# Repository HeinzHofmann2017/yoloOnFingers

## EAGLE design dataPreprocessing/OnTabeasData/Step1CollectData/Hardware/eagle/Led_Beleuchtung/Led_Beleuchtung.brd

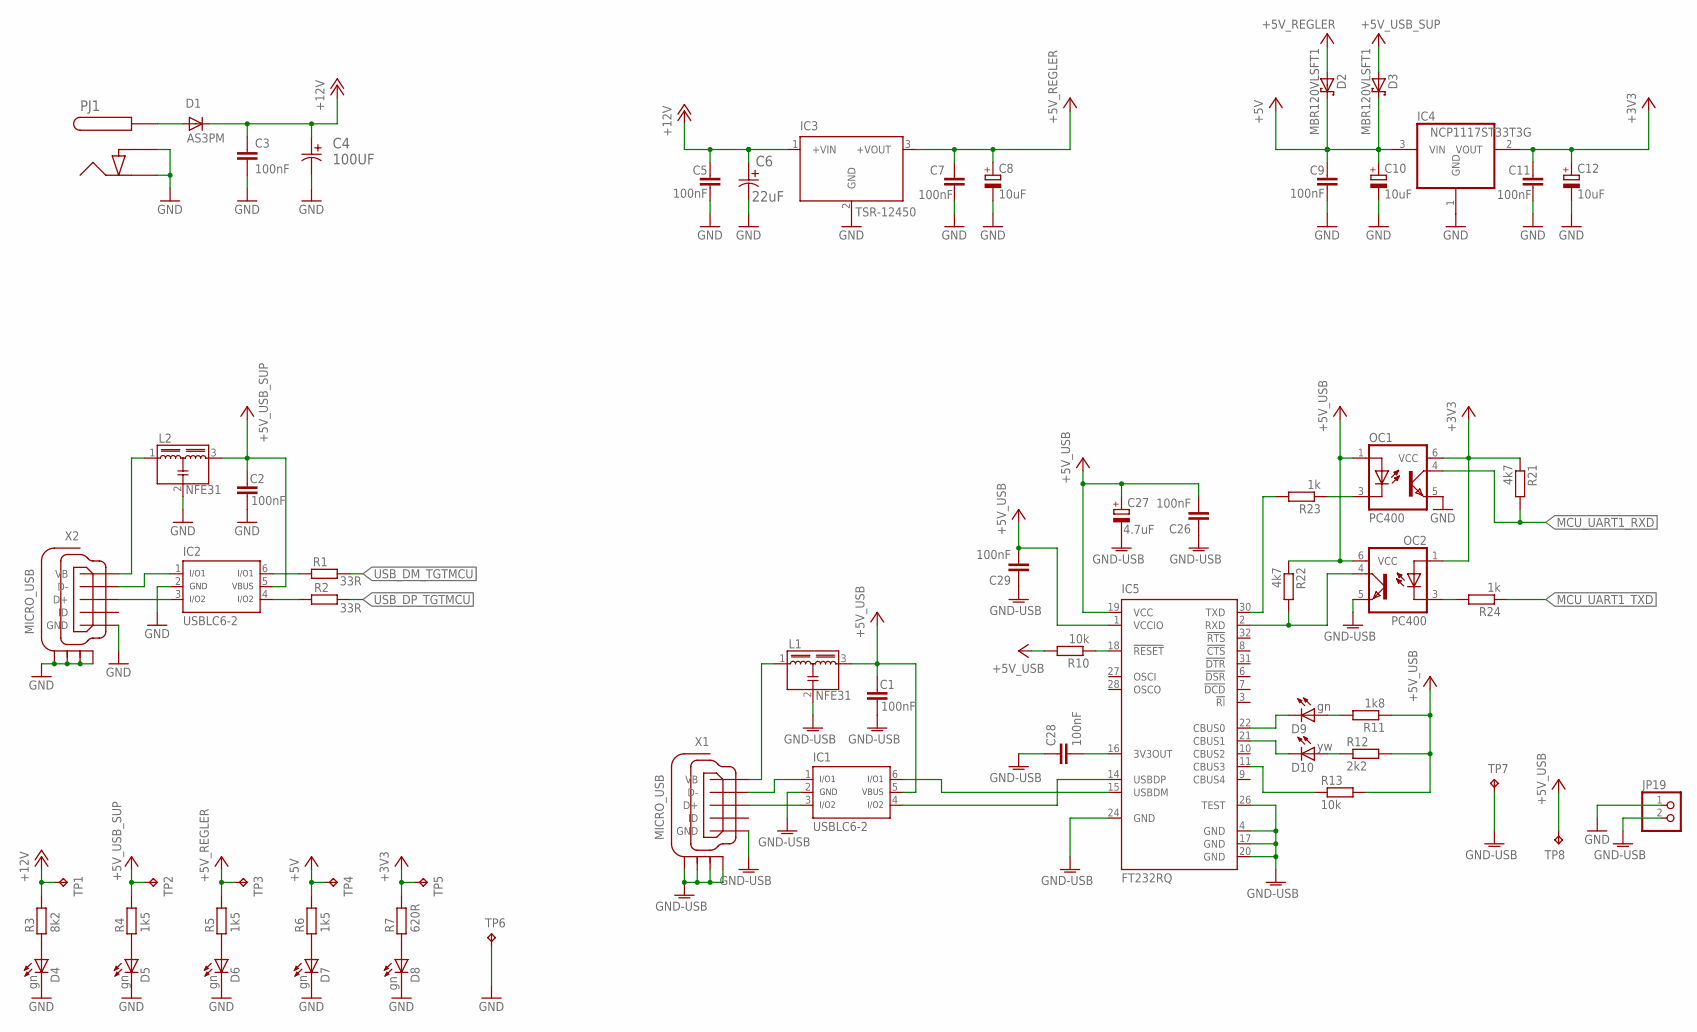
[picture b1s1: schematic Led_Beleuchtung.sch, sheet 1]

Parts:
C1, C2, C3, C5, C7, C9, C11, C26, C28: 100nF; C0603K
C4: 100UF; CAPAE660X800N
C6: 22uF; CAPAE660X610N
C8, C10, C12: 10uF; SMC_P
C27: 4.7uF; SMC_P
C29: 100nF; C0603
D1: AS3PM; TO-277A
D2, D3: MBR120VLSFT1; SOD-123
D4, D5, D6, D7, D8, D9: gn; CHIP-LED0603
D10: yw; CHIP-LED0603
IC1, IC2: USBLC6-2; SOT-23-6L
IC3: TSR-12450; TSR-1
IC4: NCP1117ST33T3G; SOT223
IC5: FT232RQ; QFN32
JP19: PINHD-1X2; 1X02
L1, L2: NFE31; EMIFILTER
OC1, OC2: PC400
PJ1: PJ-002AH-SMT-TR
R1, R2: 33R; R0603
R3: 8k2; R0603
R4, R5, R6: 1k5; R0603
R7: 620R; R0603
R10, R13: 10k; R0603
R11: 1k8; R0603
R12: 2k2; R0603
R21, R22: 4k7; R0603
R23, R24: 1k; R0603
TP1: +12V; TP08R
TP2: +5V_USB; TP08R
TP3: +5V_Reg; TP08R
TP4, TP8: +5V; TP08R
TP5: +3V3; TP08R
TP6, TP7: GND; TP08R
X1, X2: MICRO_USB; MICRO-USB

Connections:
3V3OUT_FT232: C28.2, IC5.16 (3V3OUT)
+3V3: C11.2, C12.+, IC4.2 (VOUT), OC1.6 (VCC), OC2.1 (A), R7.2, R21.1, TP5.TP; also elsewhere on the board
+5V: C9.2, C10.+, D2.C, D3.C, IC4.3 (VIN), R6.2, TP4.TP; also elsewhere on the board
+5V_REGLER: C7.2, C8.+, D2.A, IC3.3 (+VOUT), R5.2, TP3.TP
+5V_USB: C1.2, C26.2, C27.+, C29.2, IC1.5, IC5.1 (VCCIO), IC5.19 (VCC), L1.3, OC1.1 (A), OC2.6 (VCC), R10.2, R11.1, R12.2, R13.2, R22.1, TP8.TP
+5V_USB_SUP: C2.2, D3.A, IC2.5, L2.3, R4.2, TP2.TP
+12V: C3.2, C4.1, C5.2, C6.1, D1.C, IC3.1 (+VIN), R3.2, TP1.TP; also elsewhere on the board
GND: C2.1, C3.1, C4.2, C5.1, C6.2, C7.1, C8.-, C9.1, C10.-, C11.1, C12.-, D4.C, D5.C, D6.C, D7.C, D8.C, IC2.2, IC3.2 (GND), IC4.1 (GND), JP19.1, L2.2, OC1.5 (EMI), PJ1.2, PJ1.3, TP6.TP, X2.5 (GND), X2.GND1 (S1), X2.GND2 (S2), X2.GND3 (S3), X2.GND4 (S4); also elsewhere on the board
GND-USB: C1.1, C26.1, C27.-, C28.1, C29.1, IC1.2, IC5.4 (GND), IC5.17 (GND), IC5.20 (GND), IC5.24 (GND), IC5.26 (TEST), JP19.2, L1.2, OC2.5 (EMI), TP7.TP, X1.5 (GND), X1.GND1 (S1), X1.GND2 (S2), X1.GND3 (S3), X1.GND4 (S4)
MCU_UART1_RXD: OC1.4 (COL), R21.2; also elsewhere on the board
MCU_UART1_TXD: R24.1; also elsewhere on the board
unnamed: IC5.18 (!RESET), R10.1
unnamed: D9.C, IC5.22 (CBUS0)
unnamed: L1.1, X1.1 (VB)
unnamed: IC1.1, X1.2 (D-)
unnamed: IC1.3, X1.3 (D+)
unnamed: D4.A, R3.1
unnamed: L2.1, X2.1 (VB)
unnamed: D5.A, R4.1
unnamed: D10.C, IC5.21 (CBUS1)
unnamed: D10.A, R12.1
unnamed: D9.A, R11.2
unnamed: IC5.11 (CBUS3), R13.1
unnamed: IC2.1, X2.2 (D-)
unnamed: IC2.3, X2.3 (D+)
unnamed: IC2.4, R2.1
unnamed: IC2.6, R1.1
unnamed: D6.A, R5.1
unnamed: D1.A1 (A), D1.A2 (A), PJ1.1.1 (1), PJ1.1.2 (1)
unnamed: D7.A, R6.1
unnamed: D8.A, R7.1
unnamed: OC1.3 (C), R23.1
unnamed: OC2.3 (C), R24.2
unnamed: IC5.30 (TXD), R23.2
unnamed: IC5.2 (RXD), OC2.4 (COL), R22.2
USB_DM_FT232: IC1.6, IC5.15 (USBDM)
USB_DM_TGTMCU: R1.2; also elsewhere on the board
USB_DP_FT232: IC1.4, IC5.14 (USBDP)
USB_DP_TGTMCU: R2.2; also elsewhere on the board

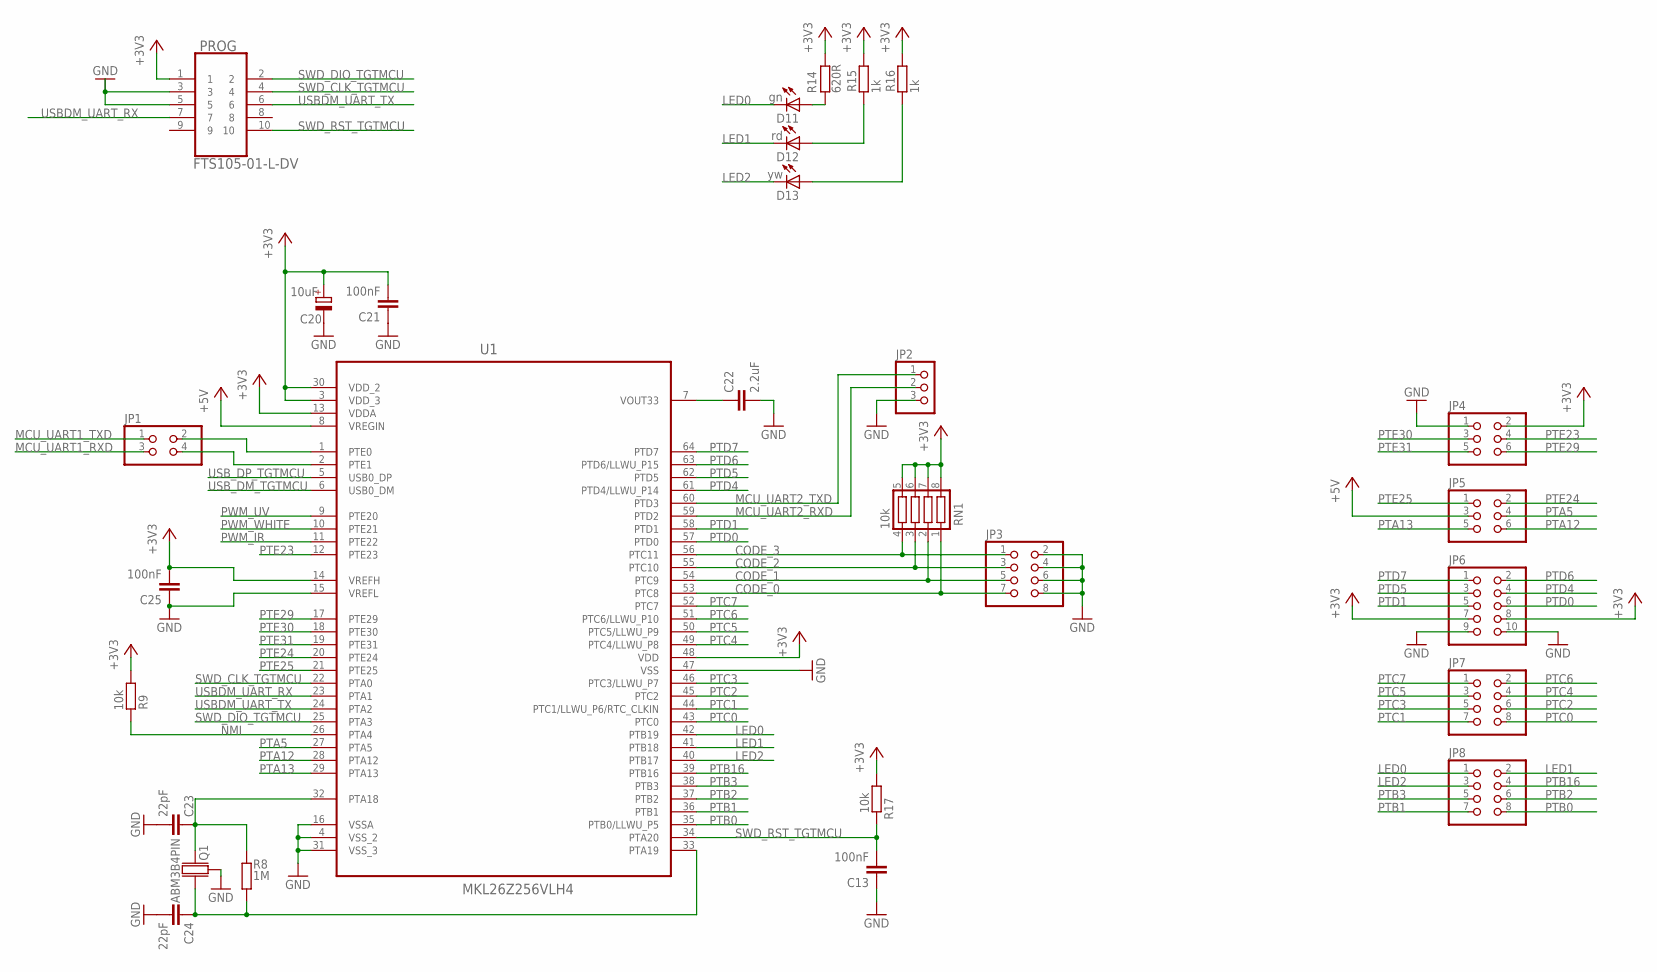
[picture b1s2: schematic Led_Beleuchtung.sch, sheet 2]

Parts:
C13, C21: 100nF; C0603
C20: 10uF; SMC_P
C22: 2.2uF; C0603
C23, C24: 22pF; C0603
C25: 100nF; C0603K
D11: gn; CHIP-LED0603
D12: rd; CHIP-LED0603
D13: yw; CHIP-LED0603
JP1: PINHD-2X2; 2X02
JP2: BCH-381H-3GN
JP3, JP7, JP8: PINHD-2X4; 2X04
JP4, JP5: PINHD-2X3; 2X03
JP6: PINHD-2X5; 2X05
PROG: FTS105-01-L-DV; SAMTEC_FTS105-01-L-DV
Q1: ABM3B4PIN; ABM3B
R8: 1M; R0603
R9, R17: 10k; R0603
R14: 620R; R0603
R15, R16: 1k; R0603
RN1: 10k; CTS742C083
U1: MKL26Z256VLH4; QFP50P1200X1200X160-64N

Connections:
+3V3: C20.+, C21.2, C25.2, JP4.2, JP6.7, JP6.8, PROG.1, R9.1, R14.2, R15.2, R16.2, R17.1, RN1.5, RN1.6, RN1.7, RN1.8, U1.3 (VDD_3), U1.13 (VDDA), U1.14 (VREFH), U1.30 (VDD_2), U1.48 (VDD); also elsewhere on the board
+5V: JP5.3, U1.8 (VREGIN); also elsewhere on the board
CODE_0: JP3.7, RN1.1, U1.53 (PTC8)
CODE_1: JP3.5, RN1.2, U1.54 (PTC9)
CODE_2: JP3.3, RN1.3, U1.55 (PTC10)
CODE_3: JP3.1, RN1.4, U1.56 (PTC11)
GND: C13.1, C20.-, C21.1, C22.2, C23.2, C24.2, C25.1, JP2.3, JP3.2, JP3.4, JP3.6, JP3.8, JP4.1, JP6.9, JP6.10, PROG.3, PROG.5, Q1.GND1 (GND), Q1.GND2 (GND), U1.4 (VSS_2), U1.15 (VREFL), U1.16 (VSSA), U1.31 (VSS_3), U1.47 (VSS); also elsewhere on the board
LED0: D11.C, JP8.1, U1.42 (PTB19)
LED1: D12.C, JP8.2, U1.41 (PTB18)
LED2: D13.C, JP8.3, U1.40 (PTB17)
MCU_UART1_RXD: JP1.3; also elsewhere on the board
MCU_UART1_TXD: JP1.1; also elsewhere on the board
MCU_UART2_RXD: JP2.2, U1.59 (PTD2)
MCU_UART2_TXD: JP2.1, U1.60 (PTD3)
unnamed: C23.1, Q1.1, R8.2, U1.32 (PTA18)
unnamed: C24.1, Q1.3 (2), R8.1, U1.33 (PTA19)
unnamed: D11.A, R14.1
unnamed: D12.A, R15.1
unnamed: D13.A, R16.1
unnamed: C22.1, U1.7 (VOUT33)
unnamed: JP1.2, U1.1 (PTE0)
unnamed: JP1.4, U1.2 (PTE1)
NMI: R9.2, U1.26 (PTA4)
PTA5: JP5.4, U1.27 (PTA5)
PTA12: JP5.6, U1.28 (PTA12)
PTA13: JP5.5, U1.29 (PTA13)
PTB0: JP8.8, U1.35 (PTB0/LLWU_P5)
PTB1: JP8.7, U1.36 (PTB1)
PTB2: JP8.6, U1.37 (PTB2)
PTB3: JP8.5, U1.38 (PTB3)
PTB16: JP8.4, U1.39 (PTB16)
PTC0: JP7.8, U1.43 (PTC0)
PTC1: JP7.7, U1.44 (PTC1/LLWU_P6/RTC_CLKIN)
PTC2: JP7.6, U1.45 (PTC2)
PTC3: JP7.5, U1.46 (PTC3/LLWU_P7)
PTC4: JP7.4, U1.49 (PTC4/LLWU_P8)
PTC5: JP7.3, U1.50 (PTC5/LLWU_P9)
PTC6: JP7.2, U1.51 (PTC6/LLWU_P10)
PTC7: JP7.1, U1.52 (PTC7)
PTD0: JP6.6, U1.57 (PTD0)
PTD1: JP6.5, U1.58 (PTD1)
PTD4: JP6.4, U1.61 (PTD4/LLWU_P14)
PTD5: JP6.3, U1.62 (PTD5)
PTD6: JP6.2, U1.63 (PTD6/LLWU_P15)
PTD7: JP6.1, U1.64 (PTD7)
PTE23: JP4.4, U1.12 (PTE23)
PTE24: JP5.2, U1.20 (PTE24)
PTE25: JP5.1, U1.21 (PTE25)
PTE29: JP4.6, U1.17 (PTE29)
PTE30: JP4.3, U1.18 (PTE30)
PTE31: JP4.5, U1.19 (PTE31)
PWM_IR: U1.11 (PTE22); also elsewhere on the board
PWM_UV: U1.9 (PTE20); also elsewhere on the board
PWM_WHITE: U1.10 (PTE21); also elsewhere on the board
SWD_CLK_TGTMCU: PROG.4, U1.22 (PTA0)
SWD_DIO_TGTMCU: PROG.2, U1.25 (PTA3)
SWD_RST_TGTMCU: C13.2, PROG.10, R17.2, U1.34 (PTA20)
USBDM_UART_RX: PROG.7, U1.23 (PTA1)
USBDM_UART_TX: PROG.6, U1.24 (PTA2)
USB_DM_TGTMCU: U1.6 (USB0_DM); also elsewhere on the board
USB_DP_TGTMCU: U1.5 (USB0_DP); also elsewhere on the board

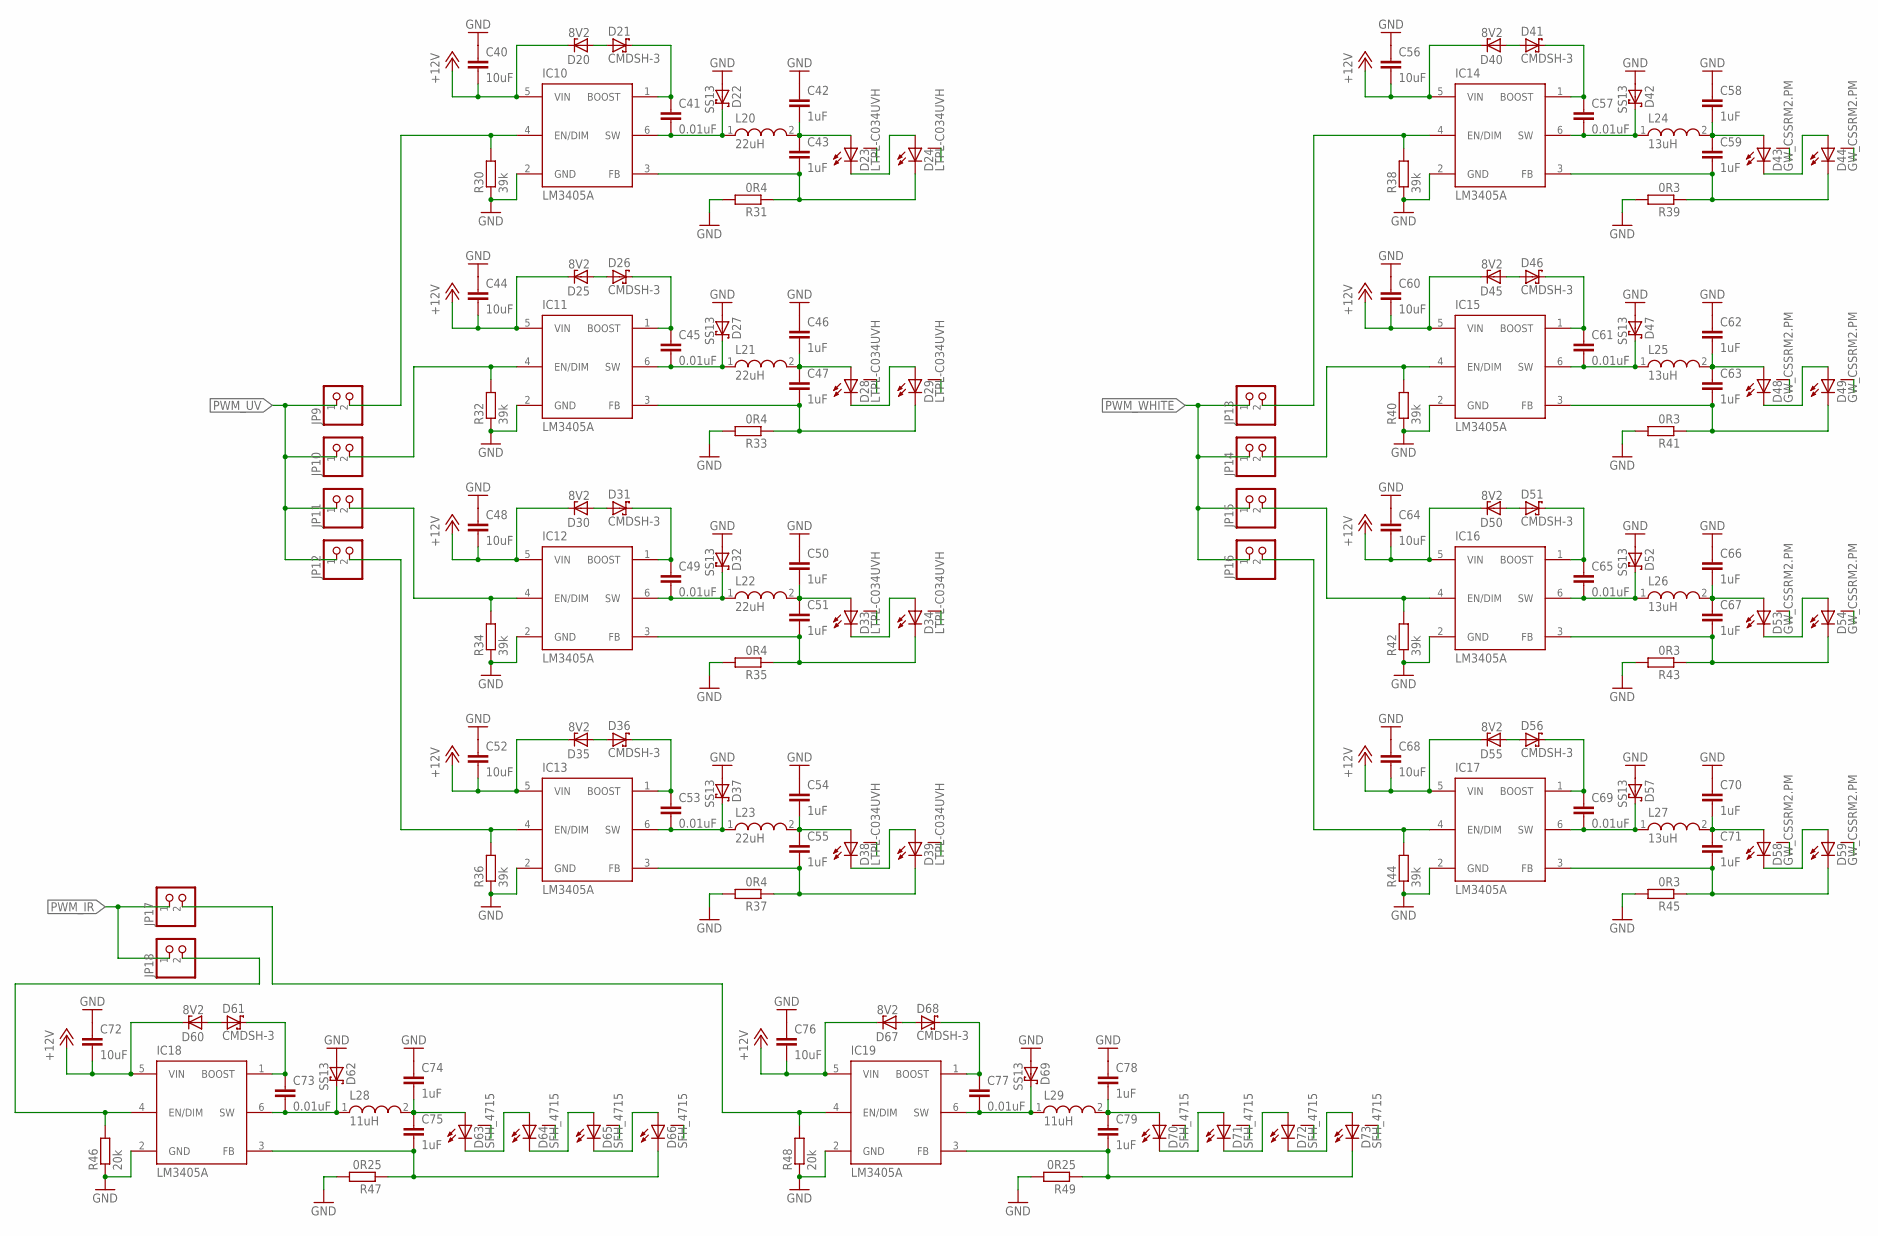
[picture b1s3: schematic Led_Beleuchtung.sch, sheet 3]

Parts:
C40, C44, C48, C52, C56, C60, C64, C68, C72, C76: 10uF; C1206K
C41, C45, C49, C53, C57, C61, C65, C69, C73, C77: 0.01uF; C0805K
C42, C43, C46, C47, C50, C51, C54, C55, C58, C59, C62, C63, C66, C67, C70, C71, C74, C75, C78, C79: 1uF; C1206K
D20, D25, D30, D35, D40, D45, D50, D55, D60, D67: 8V2; SOT23
D21, D26, D31, D36, D41, D46, D51, D56, D61, D68: CMDSH-3; SOD323
D22, D27, D32, D37, D42, D47, D52, D57, D62, D69: SS13; DO-214AC
D23, D24, D28, D29, D33, D34, D38, D39: LTPL-C034UVH
D43, D44, D48, D49, D53, D54, D58, D59: GW_CSSRM2.PM
D63, D64, D65, D66, D70, D71, D72, D73: SFH_4715
IC10, IC11, IC12, IC13, IC14, IC15, IC16, IC17, IC18, IC19: LM3405A; DDC6_SOT
JP9, JP10, JP11, JP12, JP13, JP14, JP15, JP16, JP17, JP18: PINHD-1X2; 1X02
L20, L21, L22, L23: 22uH; WE-PDF
L24, L25, L26, L27: 13uH; WE-PDF
L28, L29: 11uH; WE-PDF
R30, R32, R34, R36, R38, R40, R42, R44: 39k; R0603
R31, R33, R35, R37: 0R4; R2010
R39, R41, R43, R45: 0R3; R2010
R46, R48: 20k; R0603
R47, R49: 0R25; R2010

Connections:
+12V: C40.2, C44.2, C48.2, C52.2, C56.2, C60.2, C64.2, C68.2, C72.2, C76.2, D20.3 (C), D25.3 (C), D30.3 (C), D35.3 (C), D40.3 (C), D45.3 (C), D50.3 (C), D55.3 (C), D60.3 (C), D67.3 (C), IC10.5 (VIN), IC11.5 (VIN), IC12.5 (VIN), IC13.5 (VIN), IC14.5 (VIN), IC15.5 (VIN), IC16.5 (VIN), IC17.5 (VIN), IC18.5 (VIN), IC19.5 (VIN); also elsewhere on the board
GND: C40.1, C42.1, C44.1, C46.1, C48.1, C50.1, C52.1, C54.1, C56.1, C58.1, C60.1, C62.1, C64.1, C66.1, C68.1, C70.1, C72.1, C74.1, C76.1, C78.1, D22.A, D27.A, D32.A, D37.A, D42.A, D47.A, D52.A, D57.A, D62.A, D69.A, IC10.2 (GND), IC11.2 (GND), IC12.2 (GND), IC13.2 (GND), IC14.2 (GND), IC15.2 (GND), IC16.2 (GND), IC17.2 (GND), IC18.2 (GND), IC19.2 (GND), R30.1, R31.2, R32.1, R33.2, R34.1, R35.2, R36.1, R37.2, R38.1, R39.2, R40.1, R41.2, R42.1, R43.2, R44.1, R45.2, R46.1, R47.2, R48.1, R49.2; also elsewhere on the board
LED_WHITE8: D58.C, D59.A
unnamed: C77.1, D68.C, IC19.1 (BOOST)
unnamed: D67.1 (A), D68.A
unnamed: C77.2, D69.C, IC19.6 (SW), L29.1
unnamed: C78.2, C79.1, D70.A, L29.2
unnamed: D70.C, D71.A
unnamed: D71.C, D72.A
unnamed: D72.C, D73.A
unnamed: C79.2, D73.C, IC19.3 (FB), R49.1
unnamed: C57.1, D41.C, IC14.1 (BOOST)
unnamed: C73.1, D61.C, IC18.1 (BOOST)
unnamed: D60.1 (A), D61.A
unnamed: C73.2, D62.C, IC18.6 (SW), L28.1
unnamed: C74.2, C75.1, D63.A, L28.2
unnamed: D63.C, D64.A
unnamed: D64.C, D65.A
unnamed: D65.C, D66.A
unnamed: C75.2, D66.C, IC18.3 (FB), R47.1
unnamed: D40.1 (A), D41.A
unnamed: C57.2, D42.C, IC14.6 (SW), L24.1
unnamed: C58.2, C59.1, D43.A, L24.2
unnamed: D43.C, D44.A
unnamed: C61.1, D46.C, IC15.1 (BOOST)
unnamed: D45.1 (A), D46.A
unnamed: C59.2, D44.C, IC14.3 (FB), R39.1
unnamed: C61.2, D47.C, IC15.6 (SW), L25.1
unnamed: C62.2, C63.1, D48.A, L25.2
unnamed: D48.C, D49.A
unnamed: C63.2, D49.C, IC15.3 (FB), R41.1
unnamed: C65.1, D51.C, IC16.1 (BOOST)
unnamed: D50.1 (A), D51.A
unnamed: C65.2, D52.C, IC16.6 (SW), L26.1
unnamed: C66.2, C67.1, D53.A, L26.2
unnamed: D53.C, D54.A
unnamed: C67.2, D54.C, IC16.3 (FB), R43.1
unnamed: C69.1, D56.C, IC17.1 (BOOST)
unnamed: D55.1 (A), D56.A
unnamed: C69.2, D57.C, IC17.6 (SW), L27.1
unnamed: C70.2, C71.1, D58.A, L27.2
unnamed: C71.2, D59.C, IC17.3 (FB), R45.1
unnamed: C41.1, D21.C, IC10.1 (BOOST)
unnamed: D20.1 (A), D21.A
unnamed: C41.2, D22.C, IC10.6 (SW), L20.1
unnamed: C42.2, C43.1, D23.A, L20.2
unnamed: D23.C, D24.A
unnamed: C43.2, D24.C, IC10.3 (FB), R31.1
unnamed: C45.1, D26.C, IC11.1 (BOOST)
unnamed: D25.1 (A), D26.A
unnamed: C45.2, D27.C, IC11.6 (SW), L21.1
unnamed: C46.2, C47.1, D28.A, L21.2
unnamed: D28.C, D29.A
unnamed: C47.2, D29.C, IC11.3 (FB), R33.1
unnamed: C49.1, D31.C, IC12.1 (BOOST)
unnamed: D30.1 (A), D31.A
unnamed: C49.2, D32.C, IC12.6 (SW), L22.1
unnamed: C50.2, C51.1, D33.A, L22.2
unnamed: D33.C, D34.A
unnamed: C51.2, D34.C, IC12.3 (FB), R35.1
unnamed: C53.1, D36.C, IC13.1 (BOOST)
unnamed: D35.1 (A), D36.A
unnamed: C53.2, D37.C, IC13.6 (SW), L23.1
unnamed: C54.2, C55.1, D38.A, L23.2
unnamed: D38.C, D39.A
unnamed: C55.2, D39.C, IC13.3 (FB), R37.1
unnamed: IC10.4 (EN/DIM), JP9.2, R30.2
unnamed: IC11.4 (EN/DIM), JP10.2, R32.2
unnamed: IC12.4 (EN/DIM), JP11.2, R34.2
unnamed: IC13.4 (EN/DIM), JP12.2, R36.2
unnamed: IC14.4 (EN/DIM), JP13.2, R38.2
unnamed: IC15.4 (EN/DIM), JP14.2, R40.2
unnamed: IC16.4 (EN/DIM), JP15.2, R42.2
unnamed: IC17.4 (EN/DIM), JP16.2, R44.2
unnamed: IC18.4 (EN/DIM), JP18.2, R46.2
unnamed: IC19.4 (EN/DIM), JP17.2, R48.2
PWM_IR: JP17.1, JP18.1; also elsewhere on the board
PWM_UV: JP9.1, JP10.1, JP11.1, JP12.1; also elsewhere on the board
PWM_WHITE: JP13.1, JP14.1, JP15.1, JP16.1; also elsewhere on the board
TH_D23: D23.TH
TH_D24: D24.TH
TH_D28: D28.TH
TH_D29: D29.TH
TH_D33: D33.TH
TH_D34: D34.TH
TH_D38: D38.TH
TH_D39: D39.TH
TH_D43: D43.TH
TH_D44: D44.TH
TH_D48: D48.TH
TH_D49: D49.TH
TH_D53: D53.TH
TH_D54: D54.TH
TH_D58: D58.TH
TH_D59: D59.TH
TH_D63: D63.TH
TH_D64: D64.TH
TH_D65: D65.TH
TH_D66: D66.TH
TH_D70: D70.TH
TH_D71: D71.TH
TH_D72: D72.TH
TH_D73: D73.TH

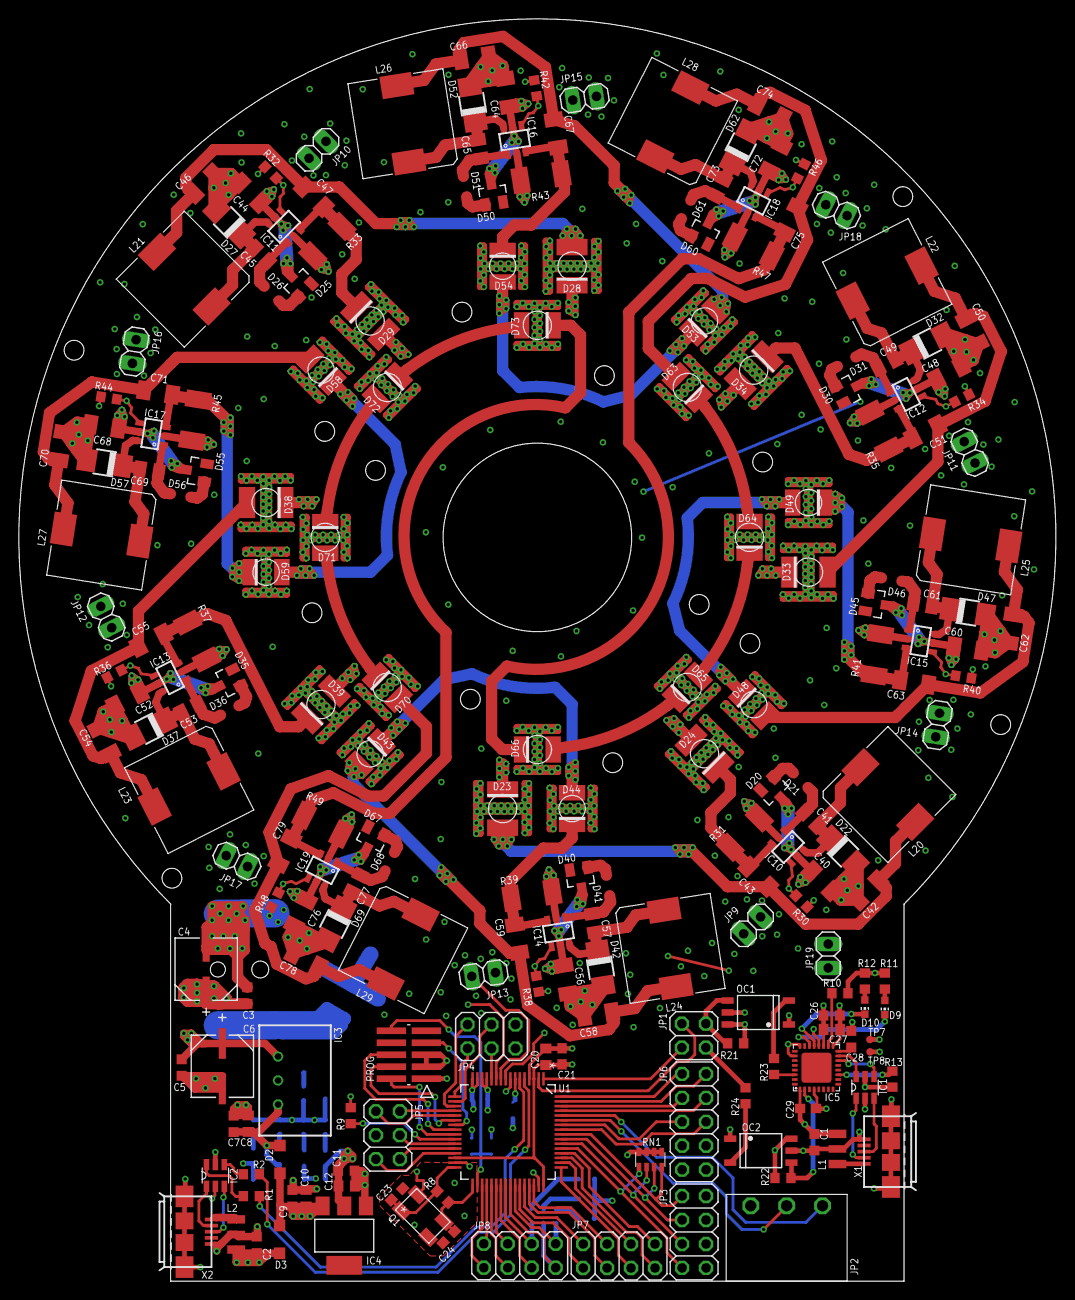
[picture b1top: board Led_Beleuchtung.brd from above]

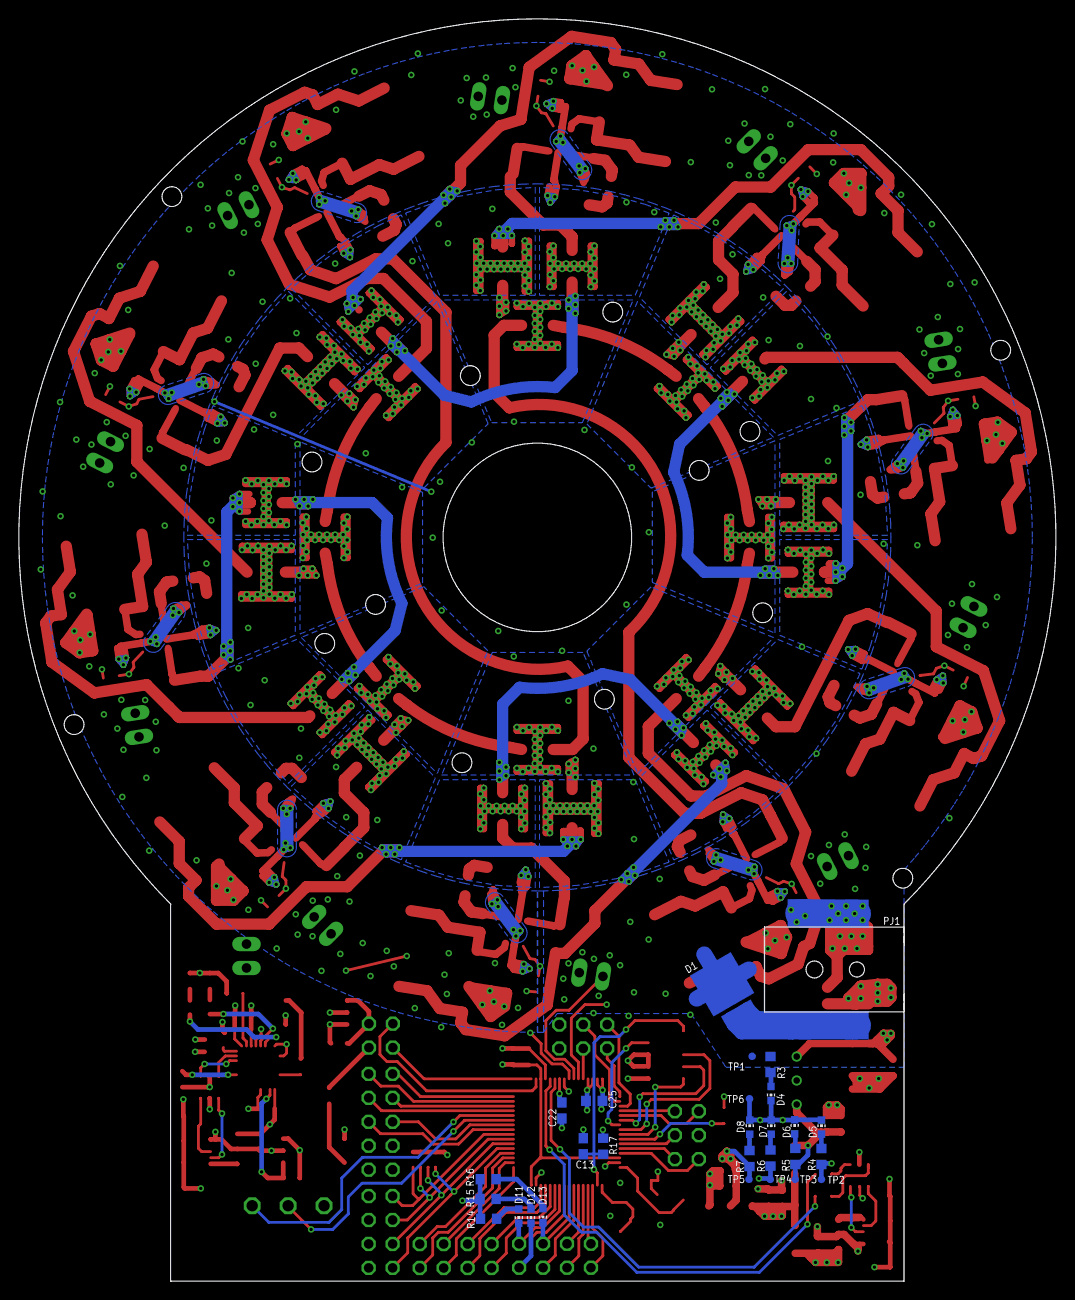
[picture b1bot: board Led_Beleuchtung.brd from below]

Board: 4 copper layers, 110.0 x 133.9 mm, 234 parts (28 on the bottom side), 167 nets.

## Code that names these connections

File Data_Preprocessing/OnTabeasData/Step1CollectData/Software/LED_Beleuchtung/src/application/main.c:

/**************************************************
    Projekt:        Led Illumination
    File:           main.c
    Date:           30.03.2017
    Author:         tmendez

    Description:    main-programm for turning
                    leds on an off via UART

**************************************************/

#include <MKL26Z4.h>
#include <MKL_EXT.h>

#include "uart.h"
#include "pwm.h"

#define LED_YELLOW  PIN_INV(PB,17)
#define LED_RED     PIN_INV(PB,18)
#define LED_GREEN   PIN_INV(PB,19)

#define CODE_0      PIN(PC,8)
#define CODE_1      PIN(PC,9)
#define CODE_2      PIN(PC,10)
#define CODE_3      PIN(PC,11)

void gpio_init(void);
void delay(void);

enum commands {UV_ON=0x81, IR_ON=0x82, WHITE_ON=0x84, OFF = 0x88};

int main(void)
{
    uint8_t error = 0;
    uint8_t timeout = 0;
    uint8_t led = 0;
    uint8_t pwmValue = 0;
    uint8_t valid = 0;
    uint8_t master = 0;

    gpio_init();
    pwm_init();
    uart_init(1,38400);
    uart_init(2,115200);
    master = ~INPUT_GET(CODE_0);

    // indicate master or slave
    if ( master == 1 ){
        OUTPUT_SET(LED_RED,POSITION_ON);
    } else {
        OUTPUT_SET(LED_YELLOW,POSITION_ON);
    }


    while(1) {

        if ( master == 1 ) {
            // Master listens at UART1 and forwards the command at UART2
            do {
                do {
                    // wait for data to receive at UART1
                    error = uart_rxChar(1, &led);
                }while(error);
                OUTPUT_SET(LED_GREEN,POSITION_ON);
                uart_rxChar(1, &pwmValue);
                pwmValue &= 0x7F;
                OUTPUT_SET(LED_GREEN,POSITION_OFF);
                switch( led ){
                    case UV_ON:     // turn on UV led
                        pwm_set(IR, 0);
                        pwm_set(WHITE, 0);
                        pwm_set(UV, pwmValue);

                        uart_txChar(2, UV_ON);
                        OUTPUT_SET(LED_GREEN,POSITION_ON);
                        uart_txChar(2, pwmValue);
                        OUTPUT_SET(LED_GREEN,POSITION_OFF);
                        valid = 1;
                        break;
                    case IR_ON:     // turn on IR led
                        pwm_set(UV, 0);
                        pwm_set(WHITE, 0);
                        pwm_set(IR, pwmValue);

                        uart_txChar(2, IR_ON);
                        OUTPUT_SET(LED_GREEN,POSITION_ON);
                        uart_txChar(2, pwmValue);
                        OUTPUT_SET(LED_GREEN,POSITION_OFF);
                        valid = 1;
                        break;
                    case WHITE_ON:  // turn on WHITE led
                        pwm_set(UV, 0);
                        pwm_set(IR, 0);
                        pwm_set(WHITE, pwmValue);

                        uart_txChar(2, WHITE_ON);
                        OUTPUT_SET(LED_GREEN,POSITION_ON);
                        uart_txChar(2, pwmValue);
                        OUTPUT_SET(LED_GREEN,POSITION_OFF);
                        valid = 1;
                        break;
                    case OFF:       // turn off leds
                        pwm_set(UV, 0);
                        pwm_set(IR, 0);
                        pwm_set(WHITE, 0);

                        uart_txChar(2, OFF);
                        OUTPUT_SET(LED_GREEN,POSITION_ON);
                        uart_txChar(2, pwmValue);
                        OUTPUT_SET(LED_GREEN,POSITION_OFF);
                        valid = 1;
                        break;
                    default:
                        // No valid command
                        uart_txChar(1,'e');
                        OUTPUT_SET(LED_GREEN,POSITION_ON);
                        uart_txChar(1,'r');
                        OUTPUT_SET(LED_GREEN,POSITION_OFF);
                        valid = 0;
                        break;
                }
            }while(valid == 0);
            valid = 0;

            // Master waits for the forwarded command to return at UART2
            // and answers at UART1
            timeout = 0;
            do{
                // wait for data to receive at UART2
                error = uart_rxChar(2, &led);
                timeout++;
            }while(error && timeout<10);
            OUTPUT_SET(LED_GREEN,POSITION_ON);
            uart_rxChar(2, &pwmValue);
            pwmValue &= 0x7F;
            OUTPUT_SET(LED_GREEN,POSITION_OFF);
            switch( led ){
                case UV_ON:
                    uart_txChar(1,UV_ON);
                    OUTPUT_SET(LED_GREEN,POSITION_ON);
                    uart_txChar(1, pwmValue);
                    OUTPUT_SET(LED_GREEN,POSITION_OFF);
                    break;
                case IR_ON:
                    uart_txChar(1,IR_ON);
                    OUTPUT_SET(LED_GREEN,POSITION_ON);
                    uart_txChar(1, pwmValue);
                    OUTPUT_SET(LED_GREEN,POSITION_OFF);
                    break;
                case WHITE_ON:
                    uart_txChar(1,WHITE_ON);
                    OUTPUT_SET(LED_GREEN,POSITION_ON);
                    uart_txChar(1, pwmValue);
                    OUTPUT_SET(LED_GREEN,POSITION_OFF);
                    break;
                case OFF:
                    uart_txChar(1,OFF);
                    OUTPUT_SET(LED_GREEN,POSITION_ON);
                    uart_txChar(1, pwmValue);
                    OUTPUT_SET(LED_GREEN,POSITION_OFF);
                    break;
                default:
                    // error occured
                    uart_txChar(1,'e');
                    OUTPUT_SET(LED_GREEN,POSITION_ON);
                    uart_txChar(1,'r');
                    OUTPUT_SET(LED_GREEN,POSITION_OFF);
                    break;
            }

        } else {

            // Slave listens at UART2 and forwards the command at UART2
            do{
                // wait for data to receive at UART2
                error = uart_rxChar(2, &led);
            }while(error);
            OUTPUT_SET(LED_GREEN,POSITION_ON);
            uart_rxChar(2, &pwmValue);
            pwmValue &= 0x7F;
            OUTPUT_SET(LED_GREEN,POSITION_OFF);
            switch( led ){
                case UV_ON:    // turn on UV led
                    pwm_set(IR, 0);
                    pwm_set(WHITE, 0);
                    pwm_set(UV, pwmValue);

                    uart_txChar(2, UV_ON);
                    OUTPUT_SET(LED_GREEN,POSITION_ON);
                    uart_txChar(2, pwmValue);
                    OUTPUT_SET(LED_GREEN,POSITION_OFF);
                    break;
                case IR_ON:    // turn on IR led
                    pwm_set(UV, 0);
                    pwm_set(WHITE, 0);
                    pwm_set(IR, pwmValue);

                    uart_txChar(2, IR_ON);
                    OUTPUT_SET(LED_GREEN,POSITION_ON);
                    uart_txChar(2, pwmValue);
                    OUTPUT_SET(LED_GREEN,POSITION_OFF);
                    break;
                case WHITE_ON:  // turn on WHITE led
                    pwm_set(UV, 0);
                    pwm_set(IR, 0);
                    pwm_set(WHITE, pwmValue);

                    uart_txChar(2, WHITE_ON);
                    OUTPUT_SET(LED_GREEN,POSITION_ON);
                    uart_txChar(2, pwmValue);
                    OUTPUT_SET(LED_GREEN,POSITION_OFF);
                    break;
                case OFF:       // turn off leds
                    pwm_set(UV, 0);
                    pwm_set(IR, 0);
                    pwm_set(WHITE, 0);

                    uart_txChar(2, OFF);
                    OUTPUT_SET(LED_GREEN,POSITION_ON);
                    uart_txChar(2, pwmValue);
                    OUTPUT_SET(LED_GREEN,POSITION_OFF);
                    break;
                default:
                    // error occured
                    uart_txChar(2,'e');
                    OUTPUT_SET(LED_GREEN,POSITION_ON);
                    uart_txChar(2,'r');
                    OUTPUT_SET(LED_GREEN,POSITION_OFF);
                    break;
            }
        }
    }
}

void gpio_init(void)
{
    // activate port-clocks
    SIM->SCGC5 =    SIM_SCGC5_PORTA_MASK |
                    SIM_SCGC5_PORTB_MASK |
                    SIM_SCGC5_PORTC_MASK |
                    SIM_SCGC5_PORTD_MASK |
                    SIM_SCGC5_PORTE_MASK;

    // init outputs of LED's
    INIT_OUTPUT(LED_YELLOW);
    OUTPUT_SET(LED_YELLOW, POSITION_OFF);
    INIT_OUTPUT(LED_RED);
    OUTPUT_SET(LED_RED, POSITION_OFF);
    INIT_OUTPUT(LED_GREEN);
    OUTPUT_SET(LED_GREEN, POSITION_OFF);

    // init inputs of master/slave-code
    INIT_INPUT_PULLUP(CODE_0);
    INIT_INPUT_PULLUP(CODE_1);
    INIT_INPUT_PULLUP(CODE_2);
    INIT_INPUT_PULLUP(CODE_3);
}

void delay(void)
{
    volatile unsigned int i,j;

    for (i = 0U; i < 5000U; i++) {
        for (j = 0U; j < 1000U; j++) {
            __asm__("nop");
        }
    }
}

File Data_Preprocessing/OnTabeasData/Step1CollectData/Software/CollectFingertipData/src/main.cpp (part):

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#define	IM_HEIGHT       960
#define N_CAMS          4

#define PWM_UV          100     // 0 ... 127
#define PWM_IR          0       // 0 ... 127
#define PWM_WHITE       40      // 0 ... 127

#define MAX_TRIALS      5

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
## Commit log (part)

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2017-10-25 probably really made the folder weights i guess
2017-10-25 just another string with numbers fixed
2017-10-25 bug in if-statement line 472 fixed, because of this this if statement never entered
2017-10-25 edited the code, so that the model will be saved in the share-Folder an not in the repository
2017-11-02 code merged together in one Repository(little cleanup)
2017-11-02 Versuch Hannes
2017-11-02 made condition for cropping data
2017-11-02 deletet old Pretrainingyolo directory...again..
2017-11-02 changed file to better work on relative-paths
2017-11-02 made second file for hannes s Test
2017-11-02 made function to convert pictures to grayscale with zeropadded minimumsize of 244*244
2017-11-03 better runtime-variables
2017-11-03 made validation for testset in % to test how accurate my model is
2017-11-03 rised badgesize up to 64 just to try
2017-11-03 reduced number of epochs, until model is saved again
2017-11-03 print the true prediction vector to shell
2017-11-03 changed the learning rate
2017-11-03 new order for scripts to run docker container
2017-11-03 some path correctures
2017-11-03 made second file to learn with higher learnrate
2017-11-03 corrected something wrong with the mailer
2017-11-06 changed name of shell-script
2017-11-06 added gradients to graph
2017-11-06 gradient multiplicated with 1000 for visualisation.
2017-11-06 set learning rate to 1
2017-11-07 made batchnorm and function to create convolutional-layers
2017-11-07 took b from the convolutional layers, because it isn't important anymore since batchnorm and we need free memory on dgx
2017-11-07 still wasn't enough free space, make Batchsize = 1
2017-11-07 plugin batchnorm one after the other, first without batchnorm again
2017-11-07 aölsdkfj
2017-11-07 aölsf
2017-11-07 changed graphiccard
2017-11-07 made learning-rate smaller, because of histogram-crash because of infinite numbers in the third iteration and made batchsize greater from 1 to 128
2017-11-07 worked fine, now enable for ca. 10 Layers batchnorm
2017-11-07 works fine now, no Problems with memory, the problem was the other GPU was allreasy in use. Lets train now over the night
2017-11-08 testing give name to shellscript
2017-11-08 optimized training-loop, so there is no if-statement in the loop anymore
2017-11-08 little change in the name of the summarys
2017-11-09 E-Mail is now better configured, so we have the name of the model on the mail too
2017-11-09 made script for running things on gpu 3
2017-11-09 better initialized Weights
2017-11-09 fixed mistake in Graph
2017-11-09 better weight init didn't work, the gradients vanished much harder than before...
2017-11-10 little bugfix
2017-11-10 used the wrong GPU
2017-11-10 The Problem with the visualisation of the error was, that the output of the network had one dimension too much for comparing with the labels.
2017-11-10 Adam instead of gradientDescent applied
2017-11-10 reverse change that console-output will be written to logfile, because it didn't work well...
2017-11-10 made a bigger epsilon in the adam-converter, because i guess this made nans for the tensorboard
2017-11-18 batchnorm is now before relu instead after relu
2017-11-20 introduced capped grads and vars, so there should no NAN's anymore, when the Wheights from Layer 1,5 or 22 is tryed to save for tensorboard.
2017-11-21 reorganized folder-structure with shellscripts to start docker and programms.
2017-11-22 started to make trainprogramm for fingers with weights from pretraining, but there are some problems with the tensorflow saver
2017-11-22 commented out cv2, because in the docker this package isn't included...
2017-11-22 made correct path in the shell-script
2017-11-22 disabled batchnorm and dropout and hope, now there is enough space in the memory
2017-11-22 made batchSize 8 and bufferSize for shuffling 500
2017-11-22 batchsize reduced to 1 and enabled dropout again ...
2017-11-22 there was no error, but there where warnings, that performance could be better with more memory. So I changed batchsize again from 8 to 7
2017-11-22 remove biases from convolutional layers worked, so now i try to raise the batchsize again to 16
2017-11-22 either batchsize=10 didnt work, so batchsize now is 8
2017-11-22 try to reduce buffersize for shuffling, and increase batchsize instead
2017-11-22 reduced number of Epochs until model is saved from 1000 to 100
2017-11-22 got labels from pretraining to the real training, with pickle. Problem: pickle isnt in the docker container, so i have to make a own docker container now.
2017-11-23 made fully connected layers in fingertraining visible for tensorboard
2017-11-23 added batchnorm to the both fully connected layer at the end of the Graph
2017-11-23 print nr of Predicted fingers to tensorboard
2017-11-23 removed dropout from the last layer, because it is absolutely senseless there
2017-11-23 improved test again
2017-11-23 fixed something in the tests, that could cause a division by zero
2017-11-23 relu after the last fullylayer in training kicked
2017-11-23 multiply cost function for x and y error with 5 like in the yolo paper
2017-11-23 added lower and higher learningrate for Graphiccard 6 & 7
2017-11-23 dropout only in the last few layers anymore
2017-11-23 added batchnorm to last fully layer in pretraining
2017-11-24 removed summary stuff from testing
2017-11-24 changed file from which weights are loaded
2017-11-24 made sess.run for saving pictures with tensorflow
2017-11-24 try last possible trained weights and hope there is no fix output, independent from the input picture, like i have in the first two tries
2017-11-29 made everything needed to work with the new share-Memory
2017-11-30 update summary every round insted of all 1000 rounds to find bug why wheights go to infinity
2017-11-30 reduced learningrate further
2017-11-30 excluded dropout
2017-11-30 asödlf
2017-11-30 have a look at all wheights, that are bigger tha 10 in the conv layer 7
2017-11-30 there where some weights >1 so for now print wheights >1 for Layer 1,3,5,6,7,8,9
2017-11-30 initialize Wheights random instead of load them
2017-11-30 made epoch from 1 to 100
2017-11-30 fixed little bug
2017-11-30 work on fingers with dropout
2017-12-01 changed script to do test on GPU 3
2017-12-01 tested on trainingdata
2017-12-01 improved validation for tensorboard
2017-12-01 print out the different values for probability and confidence
2017-12-02 made the pretraining learn with 0.0001 Learningrate and do dropout on the last few Layers instead of only the last fully connected Layer.
2017-12-05 step back from Adam to SGD, make new input for file with randomSeed, make for every Model own folder for weight-saving
2017-12-05 made test with probability*confidence and prints square, for the highest score per picture
2017-12-06 wrote function is_finite wrong..
2017-12-06 changed everything in the training after the model back to float32 and switched back to Adam instead of SGD
2017-12-06 other false float16
2017-12-07 only 10 epochs until save model int training 4
2017-12-07 try float32 with batchsize 6
2017-12-07 resized input-pictures for better GPU-Performance
2017-12-07 problemfix with float32/16 problems...
2017-12-07 raised batchsize to 12
2017-12-07 raised batchsize to 128
2017-12-07 raised batchsize to 60
2017-12-07 reduced batchsize from 40 to 35
2017-12-07 raised batchsize from 16 to 25, because 16 worked fine
2017-12-07 made everything in pretraining float32(with batchsize 128)
2017-12-11 made a additional visualization in Tensorboard for pretraining, to get problem with cost-Function.
2017-12-11 i fixed it wrong, now i hope it is better...
2017-12-12 fixed mistake with decision which learnrate shall be used and extended the learnrate reduction
2017-12-12 made a third tensorboard output to show scalars while learning=true
2017-12-12 test which of the functions went wrong...
2017-12-12 fixed little naming bug
2017-12-13 fixed a little dimension problem.
2017-12-13 fixed the same dimension problem again at a different place ==> lets test again
2017-12-13 capture the time failed, because there is another timeconsuming step inside, which protects it from getting good measurements. Now try to make two different summaries inside of one sess.run()
2017-12-13 maybe the problem is the random seed, so the setting of this seed is commented out
2017-12-13 deleted the seed from the shell-scripts too
2017-12-13 reduced buffersizes for testing
2017-12-13 raised buffersize from 1 to 2
2017-12-13 changed buffersize again..
2017-12-13 shuffle-buffersize from 5 to 4
2017-12-13 commendted out the dataset.repeat function... just to try
2017-12-13 changed buffersize from 2 to 3
2017-12-13 changed shuffelbuffersize from 4 to 5
2017-12-13 changed something before to the newer version, but because we are using tf1.4, i had to change backwards again...
2017-12-15 made the pretraining reducing it's learnrate too first time after 250000 Steps, second time after 350000 Steps
2017-12-15 fixed syntax-bug$
2017-12-15 changed Test of Probability from 0.98 to 0.995
2017-12-16 multiplied height and width with 3, because they where too small...
2017-12-19 changed in the pretraining the check, if the learnrate is adapted for shure. On the one hand, all epochs the learnrate will be printed to the screen and on the other Hand the learnrate will be saved 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
2017-12-19 fixed datatype bug
2017-12-19 label, confidence and probability-box drawing to the picture, change multiplication of Labelswidth ang labelheibelheighti back to 4
2017-12-20 changed again the multiplicationfactor from 4 to 3, which makes label-box higher and wider.
2017-12-21 made mistake with shutdown the program, so i have to do the test now on GPU2
2017-12-21 fixed the learnrate-reduction for training too
2017-12-21 now that the learningrate will be written to tensorboard, the learningrate must be part of the feed_dict, when running the sess.run to write all summaries to the tensorboard
2017-12-21 made calculation of distance and mean in range between 0 and 1
2017-12-27 improved distance-calculation again, because there was a bias: When there is a picture with no finger detected, then automatically the distance is set to zero, but this results in a mean over the who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
2017-12-27 tried again..
2017-12-27 there was someone, which said, the mask in tf.boolean_mask() mustn't be a tensorflow array. So i try now his fix
2017-12-27 try with .set_shape([None])
2017-12-27 now it works fine, i removed testcases from code
2017-12-28 made some histogramms for the documentation
2017-12-28 made training fully-dropout too...
2017-12-28 try to fix issue with different vector-length, caused by changed batchSize
2017-12-28 pretraining with full dropout now works, because batchsize is now 100. Because of this, i'm now able to raise the duration of one epoche.
2017-12-28 batchSize=10 worked fine, so try batchSize=13
2018-01-01 Made Chapter with Results and first picture imports
2018-01-02 disabled dropout for the convolutional layers in the training again
2018-01-02 wrote at the Documentation in the Einleitung
2018-01-03 Made documentation able to work with different files. And made 9000er Dataset ready to learn
2018-01-04 enabled GPU4 to learn on 9000er Set too.
2018-01-04 renewed the whole pipeline and now want to try, if everything still works fine with learning...
2018-01-04 6000er set and 9000er Set also flew through the new Data Preprocessing-Pipeline
2018-01-09 display the histogram of the x-difference and the y-difference itself to know if there is a bias...
2018-01-10 Made a Bibliography in the Documentation and draw a cube of the predictions
2018-01-12 finished making overall structure of the whole work.
2018-01-15 Pretraining documented, made Architecture Lists and first Pictures of the Tensorboard
2018-01-18 wrote a huge part in the Architecture-Chapter and made a new table
2018-01-23 Kapitel Kostenfunktion fertig geschrieben
2018-01-24 finished up with the Einleitung in the documentation
2018-01-28 made first correction-iteration over the documentation(reviewed by myself)
2018-02-05 complete improvement of the documentation after commentation from Christian. Partly improvement(until page 26) after commentation from Fabi
2018-02-06 finished up the documentation completely
2018-02-07 deleted the keras-yolo model
2018-02-08 cleaned up training-Code
2018-02-08 cleaned up the analyse_Fingerset

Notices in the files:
parts and their libraries:
EAGLE-POWER_MAGNETICS-rev17a: Copyright: Würth Elektronik
